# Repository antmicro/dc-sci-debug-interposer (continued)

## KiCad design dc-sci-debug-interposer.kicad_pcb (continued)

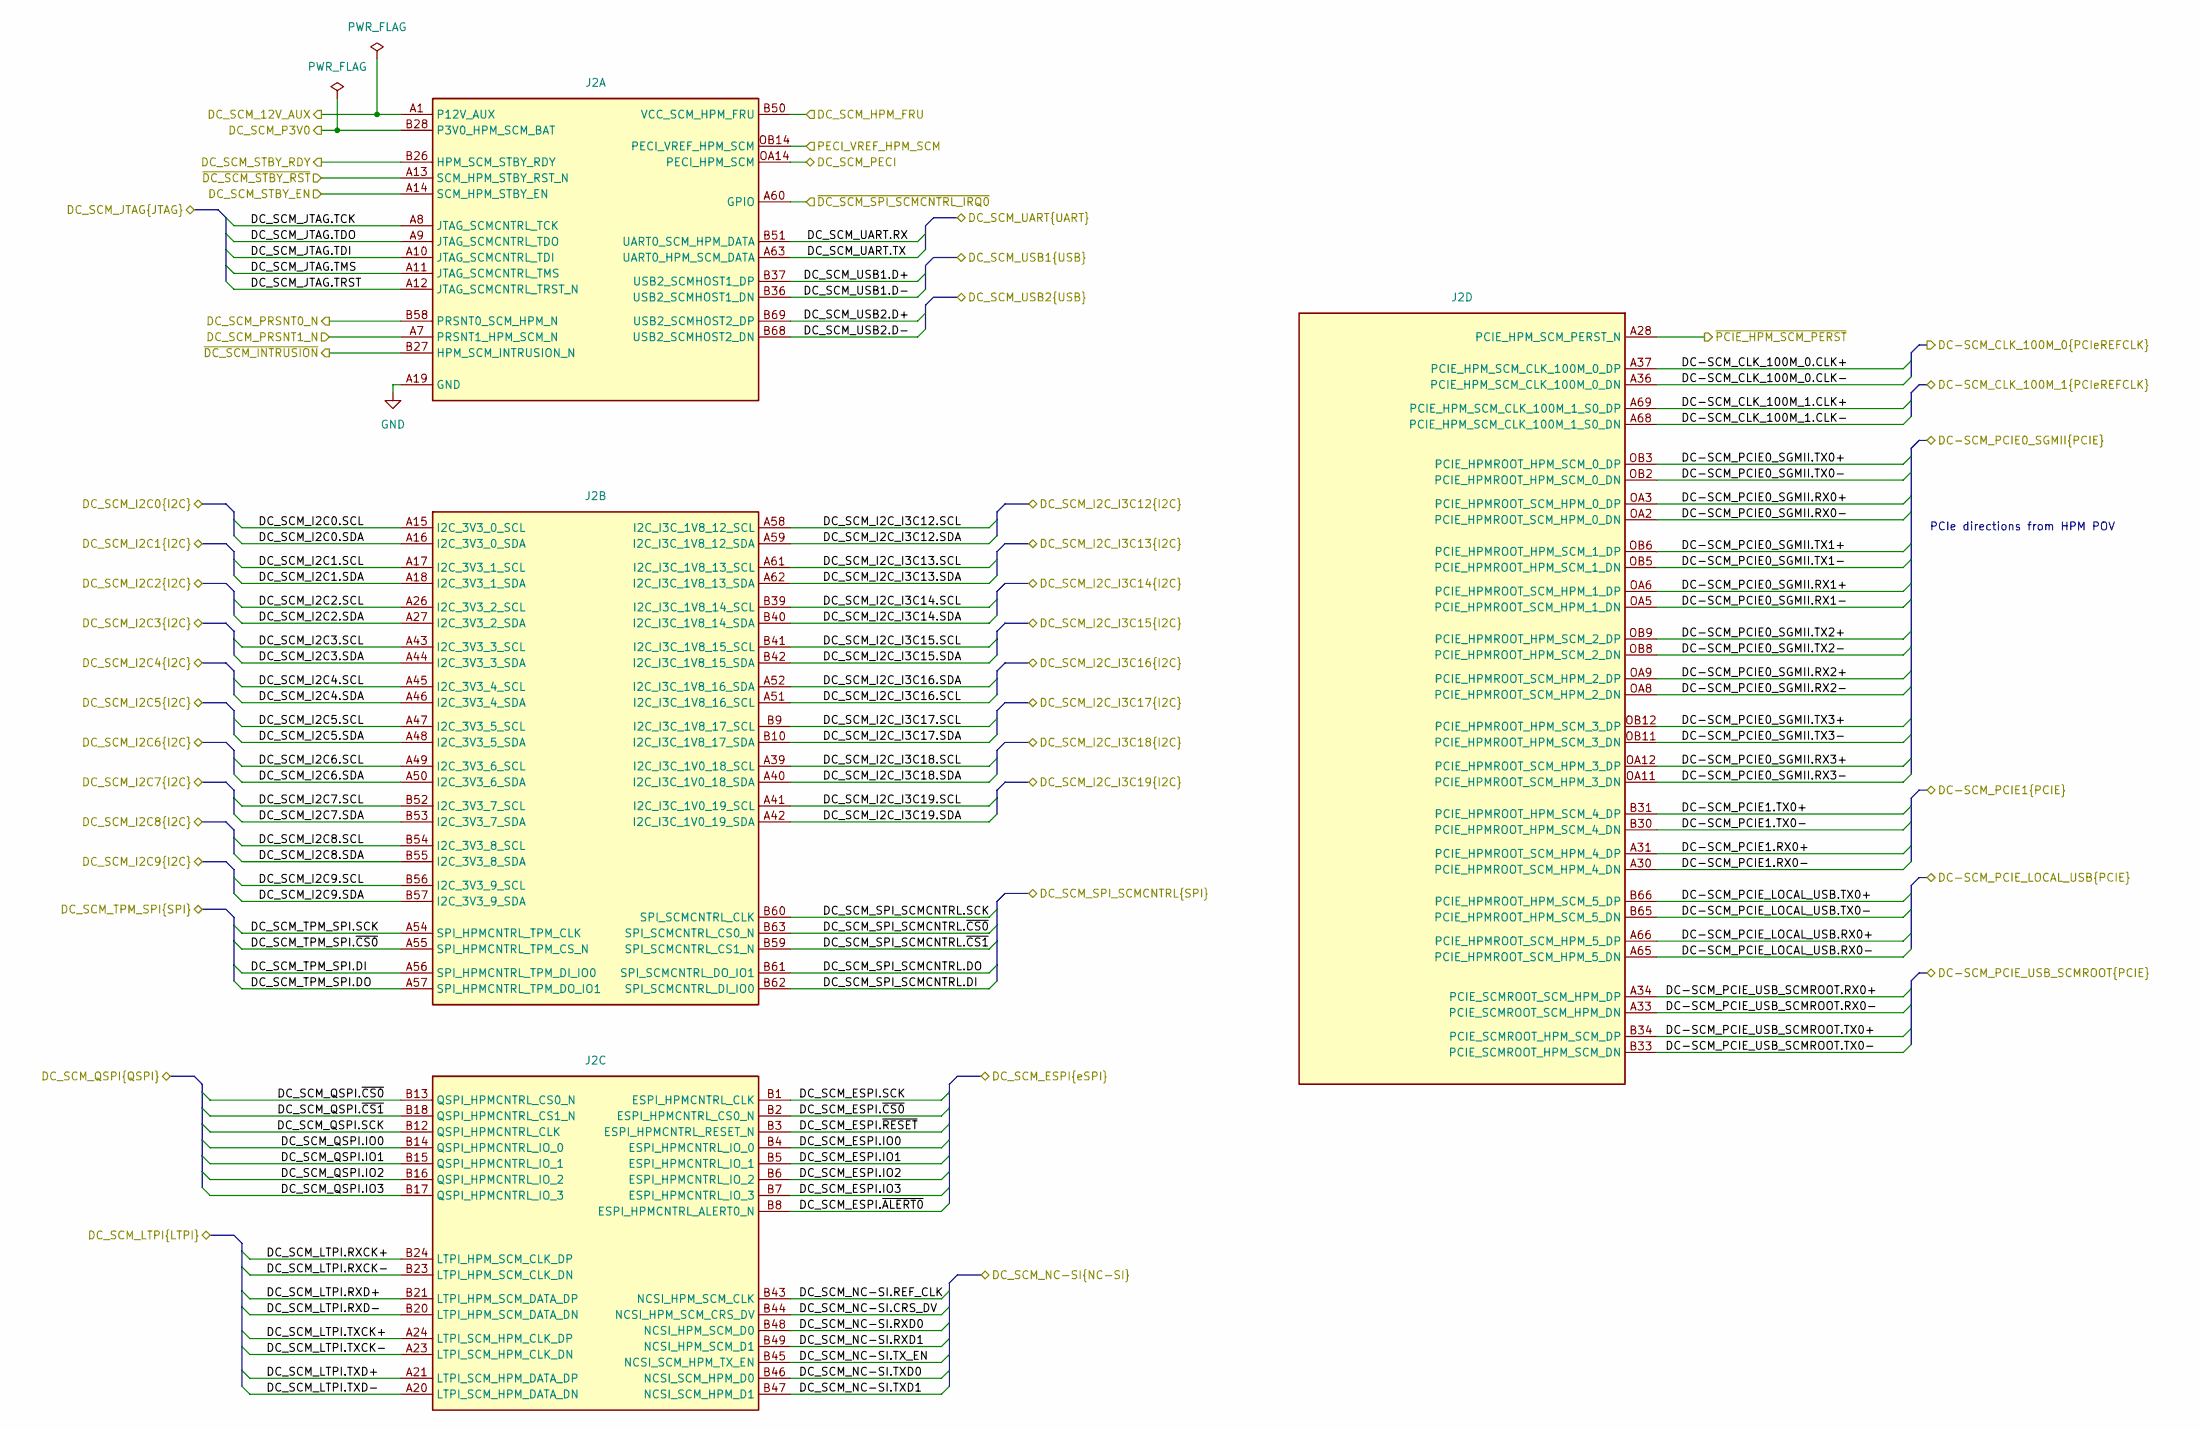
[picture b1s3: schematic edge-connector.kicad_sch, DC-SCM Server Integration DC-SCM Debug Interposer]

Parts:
J2: PCB-Edge_DC-SCM-2.1_2x84_Rev-1-1

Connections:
/DC-SCI edge connector/DC-SCM_CLK_100M_0.CLK+: J2.A37 (PCIE_HPM_SCM_CLK_100M_0_DP); also elsewhere on the board
/DC-SCI edge connector/DC-SCM_CLK_100M_0.CLK-: J2.A36 (PCIE_HPM_SCM_CLK_100M_0_DN); also elsewhere on the board
/DC-SCI edge connector/DC-SCM_CLK_100M_1.CLK+: J2.A69 (PCIE_HPM_SCM_CLK_100M_1_S0_DP); also elsewhere on the board
/DC-SCI edge connector/DC-SCM_CLK_100M_1.CLK-: J2.A68 (PCIE_HPM_SCM_CLK_100M_1_S0_DN); also elsewhere on the board
/DC-SCI edge connector/DC-SCM_PCIE0_SGMII.RX0+: J2.OA3 (PCIE_HPMROOT_SCM_HPM_0_DP); also elsewhere on the board
/DC-SCI edge connector/DC-SCM_PCIE0_SGMII.RX0-: J2.OA2 (PCIE_HPMROOT_SCM_HPM_0_DN); also elsewhere on the board
/DC-SCI edge connector/DC-SCM_PCIE0_SGMII.RX1+: J2.OA6 (PCIE_HPMROOT_SCM_HPM_1_DP); also elsewhere on the board
/DC-SCI edge connector/DC-SCM_PCIE0_SGMII.RX1-: J2.OA5 (PCIE_HPMROOT_SCM_HPM_1_DN); also elsewhere on the board
/DC-SCI edge connector/DC-SCM_PCIE0_SGMII.RX2+: J2.OA9 (PCIE_HPMROOT_SCM_HPM_2_DP); also elsewhere on the board
/DC-SCI edge connector/DC-SCM_PCIE0_SGMII.RX2-: J2.OA8 (PCIE_HPMROOT_SCM_HPM_2_DN); also elsewhere on the board
/DC-SCI edge connector/DC-SCM_PCIE0_SGMII.RX3+: J2.OA12 (PCIE_HPMROOT_SCM_HPM_3_DP); also elsewhere on the board
/DC-SCI edge connector/DC-SCM_PCIE0_SGMII.RX3-: J2.OA11 (PCIE_HPMROOT_SCM_HPM_3_DN); also elsewhere on the board
/DC-SCI edge connector/DC-SCM_PCIE0_SGMII.TX0+: J2.OB3 (PCIE_HPMROOT_HPM_SCM_0_DP); also elsewhere on the board
/DC-SCI edge connector/DC-SCM_PCIE0_SGMII.TX0-: J2.OB2 (PCIE_HPMROOT_HPM_SCM_0_DN); also elsewhere on the board
/DC-SCI edge connector/DC-SCM_PCIE0_SGMII.TX1+: J2.OB6 (PCIE_HPMROOT_HPM_SCM_1_DP); also elsewhere on the board
/DC-SCI edge connector/DC-SCM_PCIE0_SGMII.TX1-: J2.OB5 (PCIE_HPMROOT_HPM_SCM_1_DN); also elsewhere on the board
/DC-SCI edge connector/DC-SCM_PCIE0_SGMII.TX2+: J2.OB9 (PCIE_HPMROOT_HPM_SCM_2_DP); also elsewhere on the board
/DC-SCI edge connector/DC-SCM_PCIE0_SGMII.TX2-: J2.OB8 (PCIE_HPMROOT_HPM_SCM_2_DN); also elsewhere on the board
/DC-SCI edge connector/DC-SCM_PCIE0_SGMII.TX3+: J2.OB12 (PCIE_HPMROOT_HPM_SCM_3_DP); also elsewhere on the board
/DC-SCI edge connector/DC-SCM_PCIE0_SGMII.TX3-: J2.OB11 (PCIE_HPMROOT_HPM_SCM_3_DN); also elsewhere on the board
/DC-SCI edge connector/DC-SCM_PCIE1.RX0+: J2.A31 (PCIE_HPMROOT_SCM_HPM_4_DP); also elsewhere on the board
/DC-SCI edge connector/DC-SCM_PCIE1.RX0-: J2.A30 (PCIE_HPMROOT_SCM_HPM_4_DN); also elsewhere on the board
/DC-SCI edge connector/DC-SCM_PCIE1.TX0+: J2.B31 (PCIE_HPMROOT_HPM_SCM_4_DP); also elsewhere on the board
/DC-SCI edge connector/DC-SCM_PCIE1.TX0-: J2.B30 (PCIE_HPMROOT_HPM_SCM_4_DN); also elsewhere on the board
/DC-SCI edge connector/DC-SCM_PCIE_LOCAL_USB.RX0+: J2.A66 (PCIE_HPMROOT_SCM_HPM_5_DP); also elsewhere on the board
/DC-SCI edge connector/DC-SCM_PCIE_LOCAL_USB.RX0-: J2.A65 (PCIE_HPMROOT_SCM_HPM_5_DN); also elsewhere on the board
/DC-SCI edge connector/DC-SCM_PCIE_LOCAL_USB.TX0+: J2.B66 (PCIE_HPMROOT_HPM_SCM_5_DP); also elsewhere on the board
/DC-SCI edge connector/DC-SCM_PCIE_LOCAL_USB.TX0-: J2.B65 (PCIE_HPMROOT_HPM_SCM_5_DN); also elsewhere on the board
/DC-SCI edge connector/DC-SCM_PCIE_USB_SCMROOT.RX0+: J2.A34 (PCIE_SCMROOT_SCM_HPM_DP); also elsewhere on the board
/DC-SCI edge connector/DC-SCM_PCIE_USB_SCMROOT.RX0-: J2.A33 (PCIE_SCMROOT_SCM_HPM_DN); also elsewhere on the board
/DC-SCI edge connector/DC-SCM_PCIE_USB_SCMROOT.TX0+: J2.B34 (PCIE_SCMROOT_HPM_SCM_DP); also elsewhere on the board
/DC-SCI edge connector/DC-SCM_PCIE_USB_SCMROOT.TX0-: J2.B33 (PCIE_SCMROOT_HPM_SCM_DN); also elsewhere on the board
/DC-SCI edge connector/DC_SCM_12V_AUX: J2.A1 (P12V_AUX), J2.A2 (P12V_AUX), J2.A3 (P12V_AUX), J2.A4 (P12V_AUX); also elsewhere on the board
/DC-SCI edge connector/DC_SCM_ESPI.IO0: J2.B4 (ESPI_HPMCNTRL_IO_0); also elsewhere on the board
/DC-SCI edge connector/DC_SCM_ESPI.IO1: J2.B5 (ESPI_HPMCNTRL_IO_1); also elsewhere on the board
/DC-SCI edge connector/DC_SCM_ESPI.IO2: J2.B6 (ESPI_HPMCNTRL_IO_2); also elsewhere on the board
/DC-SCI edge connector/DC_SCM_ESPI.IO3: J2.B7 (ESPI_HPMCNTRL_IO_3); also elsewhere on the board
/DC-SCI edge connector/DC_SCM_ESPI.SCK: J2.B1 (ESPI_HPMCNTRL_CLK); also elsewhere on the board
/DC-SCI edge connector/DC_SCM_ESPI.~ALERT0: J2.B8 (ESPI_HPMCNTRL_ALERT0_N); also elsewhere on the board
/DC-SCI edge connector/DC_SCM_ESPI.~CS0: J2.B2 (ESPI_HPMCNTRL_CS0_N); also elsewhere on the board
/DC-SCI edge connector/DC_SCM_ESPI.~RESET: J2.B3 (ESPI_HPMCNTRL_RESET_N); also elsewhere on the board
/DC-SCI edge connector/DC_SCM_HPM_FRU: J2.B50 (VCC_SCM_HPM_FRU); also elsewhere on the board
/DC-SCI edge connector/DC_SCM_I2C0.SCL: J2.A15 (I2C_3V3_0_SCL); also elsewhere on the board
/DC-SCI edge connector/DC_SCM_I2C0.SDA: J2.A16 (I2C_3V3_0_SDA); also elsewhere on the board
/DC-SCI edge connector/DC_SCM_I2C1.SCL: J2.A17 (I2C_3V3_1_SCL); also elsewhere on the board
/DC-SCI edge connector/DC_SCM_I2C1.SDA: J2.A18 (I2C_3V3_1_SDA); also elsewhere on the board
/DC-SCI edge connector/DC_SCM_I2C2.SCL: J2.A26 (I2C_3V3_2_SCL); also elsewhere on the board
/DC-SCI edge connector/DC_SCM_I2C2.SDA: J2.A27 (I2C_3V3_2_SDA); also elsewhere on the board
/DC-SCI edge connector/DC_SCM_I2C3.SCL: J2.A43 (I2C_3V3_3_SCL); also elsewhere on the board
/DC-SCI edge connector/DC_SCM_I2C3.SDA: J2.A44 (I2C_3V3_3_SDA); also elsewhere on the board
/DC-SCI edge connector/DC_SCM_I2C4.SCL: J2.A45 (I2C_3V3_4_SCL); also elsewhere on the board
/DC-SCI edge connector/DC_SCM_I2C4.SDA: J2.A46 (I2C_3V3_4_SDA); also elsewhere on the board
/DC-SCI edge connector/DC_SCM_I2C5.SCL: J2.A47 (I2C_3V3_5_SCL); also elsewhere on the board
/DC-SCI edge connector/DC_SCM_I2C5.SDA: J2.A48 (I2C_3V3_5_SDA); also elsewhere on the board
/DC-SCI edge connector/DC_SCM_I2C6.SCL: J2.A49 (I2C_3V3_6_SCL); also elsewhere on the board
/DC-SCI edge connector/DC_SCM_I2C6.SDA: J2.A50 (I2C_3V3_6_SDA); also elsewhere on the board
/DC-SCI edge connector/DC_SCM_I2C7.SCL: J2.B52 (I2C_3V3_7_SCL); also elsewhere on the board
/DC-SCI edge connector/DC_SCM_I2C7.SDA: J2.B53 (I2C_3V3_7_SDA); also elsewhere on the board
/DC-SCI edge connector/DC_SCM_I2C8.SCL: J2.B54 (I2C_3V3_8_SCL); also elsewhere on the board
/DC-SCI edge connector/DC_SCM_I2C8.SDA: J2.B55 (I2C_3V3_8_SDA); also elsewhere on the board
/DC-SCI edge connector/DC_SCM_I2C9.SCL: J2.B56 (I2C_3V3_9_SCL); also elsewhere on the board
/DC-SCI edge connector/DC_SCM_I2C9.SDA: J2.B57 (I2C_3V3_9_SDA); also elsewhere on the board
/DC-SCI edge connector/DC_SCM_I2C_I3C12.SCL: J2.A58 (I2C_I3C_1V8_12_SCL); also elsewhere on the board
/DC-SCI edge connector/DC_SCM_I2C_I3C12.SDA: J2.A59 (I2C_I3C_1V8_12_SDA); also elsewhere on the board
/DC-SCI edge connector/DC_SCM_I2C_I3C13.SCL: J2.A61 (I2C_I3C_1V8_13_SCL); also elsewhere on the board
/DC-SCI edge connector/DC_SCM_I2C_I3C13.SDA: J2.A62 (I2C_I3C_1V8_13_SDA); also elsewhere on the board
/DC-SCI edge connector/DC_SCM_I2C_I3C14.SCL: J2.B39 (I2C_I3C_1V8_14_SCL); also elsewhere on the board
/DC-SCI edge connector/DC_SCM_I2C_I3C14.SDA: J2.B40 (I2C_I3C_1V8_14_SDA); also elsewhere on the board
/DC-SCI edge connector/DC_SCM_I2C_I3C15.SCL: J2.B41 (I2C_I3C_1V8_15_SCL); also elsewhere on the board
/DC-SCI edge connector/DC_SCM_I2C_I3C15.SDA: J2.B42 (I2C_I3C_1V8_15_SDA); also elsewhere on the board
/DC-SCI edge connector/DC_SCM_I2C_I3C16.SCL: J2.A51 (I2C_I3C_1V8_16_SCL); also elsewhere on the board
/DC-SCI edge connector/DC_SCM_I2C_I3C16.SDA: J2.A52 (I2C_I3C_1V8_16_SDA); also elsewhere on the board
/DC-SCI edge connector/DC_SCM_I2C_I3C17.SCL: J2.B9 (I2C_I3C_1V8_17_SCL); also elsewhere on the board
/DC-SCI edge connector/DC_SCM_I2C_I3C17.SDA: J2.B10 (I2C_I3C_1V8_17_SDA); also elsewhere on the board
/DC-SCI edge connector/DC_SCM_I2C_I3C18.SCL: J2.A39 (I2C_I3C_1V0_18_SCL); also elsewhere on the board
/DC-SCI edge connector/DC_SCM_I2C_I3C18.SDA: J2.A40 (I2C_I3C_1V0_18_SDA); also elsewhere on the board
/DC-SCI edge connector/DC_SCM_I2C_I3C19.SCL: J2.A41 (I2C_I3C_1V0_19_SCL); also elsewhere on the board
/DC-SCI edge connector/DC_SCM_I2C_I3C19.SDA: J2.A42 (I2C_I3C_1V0_19_SDA); also elsewhere on the board
/DC-SCI edge connector/DC_SCM_JTAG.TCK: J2.A8 (JTAG_SCMCNTRL_TCK); also elsewhere on the board
/DC-SCI edge connector/DC_SCM_JTAG.TDI: J2.A10 (JTAG_SCMCNTRL_TDI); also elsewhere on the board
/DC-SCI edge connector/DC_SCM_JTAG.TDO: J2.A9 (JTAG_SCMCNTRL_TDO); also elsewhere on the board
/DC-SCI edge connector/DC_SCM_JTAG.TMS: J2.A11 (JTAG_SCMCNTRL_TMS); also elsewhere on the board
/DC-SCI edge connector/DC_SCM_JTAG.TRST: J2.A12 (JTAG_SCMCNTRL_TRST_N); also elsewhere on the board
/DC-SCI edge connector/DC_SCM_LTPI.RXCK+: J2.B24 (LTPI_HPM_SCM_CLK_DP); also elsewhere on the board
/DC-SCI edge connector/DC_SCM_LTPI.RXCK-: J2.B23 (LTPI_HPM_SCM_CLK_DN); also elsewhere on the board
/DC-SCI edge connector/DC_SCM_LTPI.RXD+: J2.B21 (LTPI_HPM_SCM_DATA_DP); also elsewhere on the board
/DC-SCI edge connector/DC_SCM_LTPI.RXD-: J2.B20 (LTPI_HPM_SCM_DATA_DN); also elsewhere on the board
/DC-SCI edge connector/DC_SCM_LTPI.TXCK+: J2.A24 (LTPI_SCM_HPM_CLK_DP); also elsewhere on the board
/DC-SCI edge connector/DC_SCM_LTPI.TXCK-: J2.A23 (LTPI_SCM_HPM_CLK_DN); also elsewhere on the board
/DC-SCI edge connector/DC_SCM_LTPI.TXD+: J2.A21 (LTPI_SCM_HPM_DATA_DP); also elsewhere on the board
/DC-SCI edge connector/DC_SCM_LTPI.TXD-: J2.A20 (LTPI_SCM_HPM_DATA_DN); also elsewhere on the board
/DC-SCI edge connector/DC_SCM_NC-SI.CRS_DV: J2.B44 (NCSI_HPM_SCM_CRS_DV); also elsewhere on the board
/DC-SCI edge connector/DC_SCM_NC-SI.REF_CLK: J2.B43 (NCSI_HPM_SCM_CLK); also elsewhere on the board
/DC-SCI edge connector/DC_SCM_NC-SI.RXD0: J2.B48 (NCSI_HPM_SCM_D0); also elsewhere on the board
/DC-SCI edge connector/DC_SCM_NC-SI.RXD1: J2.B49 (NCSI_HPM_SCM_D1); also elsewhere on the board
/DC-SCI edge connector/DC_SCM_NC-SI.TXD0: J2.B46 (NCSI_SCM_HPM_D0); also elsewhere on the board
/DC-SCI edge connector/DC_SCM_NC-SI.TXD1: J2.B47 (NCSI_SCM_HPM_D1); also elsewhere on the board
/DC-SCI edge connector/DC_SCM_NC-SI.TX_EN: J2.B45 (NCSI_SCM_HPM_TX_EN); also elsewhere on the board
/DC-SCI edge connector/DC_SCM_P3V0: J2.B28 (P3V0_HPM_SCM_BAT); also elsewhere on the board
/DC-SCI edge connector/DC_SCM_PECI: J2.OA14 (PECI_HPM_SCM); also elsewhere on the board
/DC-SCI edge connector/DC_SCM_PRSNT0_N: J2.B58 (PRSNT0_SCM_HPM_N); also elsewhere on the board
/DC-SCI edge connector/DC_SCM_PRSNT1_N: J2.A7 (PRSNT1_HPM_SCM_N); also elsewhere on the board
/DC-SCI edge connector/DC_SCM_QSPI.IO0: J2.B14 (QSPI_HPMCNTRL_IO_0); also elsewhere on the board
/DC-SCI edge connector/DC_SCM_QSPI.IO1: J2.B15 (QSPI_HPMCNTRL_IO_1); also elsewhere on the board
/DC-SCI edge connector/DC_SCM_QSPI.IO2: J2.B16 (QSPI_HPMCNTRL_IO_2); also elsewhere on the board
/DC-SCI edge connector/DC_SCM_QSPI.IO3: J2.B17 (QSPI_HPMCNTRL_IO_3); also elsewhere on the board
/DC-SCI edge connector/DC_SCM_QSPI.SCK: J2.B12 (QSPI_HPMCNTRL_CLK); also elsewhere on the board
/DC-SCI edge connector/DC_SCM_QSPI.~CS0: J2.B13 (QSPI_HPMCNTRL_CS0_N); also elsewhere on the board
/DC-SCI edge connector/DC_SCM_QSPI.~CS1: J2.B18 (QSPI_HPMCNTRL_CS1_N); also elsewhere on the board
/DC-SCI edge connector/DC_SCM_SPI_SCMCNTRL.DI: J2.B62 (SPI_SCMCNTRL_DI_IO0); also elsewhere on the board
/DC-SCI edge connector/DC_SCM_SPI_SCMCNTRL.DO: J2.B61 (SPI_SCMCNTRL_DO_IO1); also elsewhere on the board
/DC-SCI edge connector/DC_SCM_SPI_SCMCNTRL.SCK: J2.B60 (SPI_SCMCNTRL_CLK); also elsewhere on the board
/DC-SCI edge connector/DC_SCM_SPI_SCMCNTRL.~CS0: J2.B63 (SPI_SCMCNTRL_CS0_N); also elsewhere on the board
/DC-SCI edge connector/DC_SCM_SPI_SCMCNTRL.~CS1: J2.B59 (SPI_SCMCNTRL_CS1_N); also elsewhere on the board
/DC-SCI edge connector/DC_SCM_STBY_EN: J2.A14 (SCM_HPM_STBY_EN); also elsewhere on the board
/DC-SCI edge connector/DC_SCM_STBY_RDY: J2.B26 (HPM_SCM_STBY_RDY); also elsewhere on the board
/DC-SCI edge connector/DC_SCM_TPM_SPI.DI: J2.A56 (SPI_HPMCNTRL_TPM_DI_IO0); also elsewhere on the board
/DC-SCI edge connector/DC_SCM_TPM_SPI.DO: J2.A57 (SPI_HPMCNTRL_TPM_DO_IO1); also elsewhere on the board
/DC-SCI edge connector/DC_SCM_TPM_SPI.SCK: J2.A54 (SPI_HPMCNTRL_TPM_CLK); also elsewhere on the board
/DC-SCI edge connector/DC_SCM_TPM_SPI.~CS0: J2.A55 (SPI_HPMCNTRL_TPM_CS_N); also elsewhere on the board
/DC-SCI edge connector/DC_SCM_UART.RX: J2.B51 (UART0_SCM_HPM_DATA); also elsewhere on the board
/DC-SCI edge connector/DC_SCM_UART.TX: J2.A63 (UART0_HPM_SCM_DATA); also elsewhere on the board
/DC-SCI edge connector/DC_SCM_USB1.D+: J2.B37 (USB2_SCMHOST1_DP); also elsewhere on the board
/DC-SCI edge connector/DC_SCM_USB1.D-: J2.B36 (USB2_SCMHOST1_DN); also elsewhere on the board
/DC-SCI edge connector/DC_SCM_USB2.D+: J2.B69 (USB2_SCMHOST2_DP); also elsewhere on the board
/DC-SCI edge connector/DC_SCM_USB2.D-: J2.B68 (USB2_SCMHOST2_DN); also elsewhere on the board
/DC-SCI edge connector/PECI_VREF_HPM_SCM: J2.OB14 (PECI_VREF_HPM_SCM); also elsewhere on the board
/DC-SCI edge connector/~DC_SCM_INTRUSION: J2.B27 (HPM_SCM_INTRUSION_N); also elsewhere on the board
/DC-SCI edge connector/~DC_SCM_SPI_SCMCNTRL_IRQ0: J2.A60 (GPIO); also elsewhere on the board
/DC-SCI edge connector/~DC_SCM_STBY_RST: J2.A13 (SCM_HPM_STBY_RST_N); also elsewhere on the board
/DC-SCI edge connector/~PCIE_HPM_SCM_PERST: J2.A28 (PCIE_HPM_SCM_PERST_N); also elsewhere on the board
GND: J2.A5 (GND), J2.A6 (GND), J2.A19 (GND), J2.A22 (GND), J2.A25 (GND), J2.A29 (GND), J2.A32 (GND), J2.A35 (GND), J2.A38 (GND), J2.A53 (GND), J2.A64 (GND), J2.A67 (GND), J2.A70 (GND), J2.B11 (GND), J2.B19 (GND), J2.B22 (GND), J2.B25 (GND), J2.B29 (GND), J2.B32 (GND), J2.B35 (GND), J2.B38 (GND), J2.B64 (GND), J2.B67 (GND), J2.B70 (GND), J2.OA1 (GND), J2.OA4 (GND), J2.OA7 (GND), J2.OA10 (GND), J2.OA13 (GND), J2.OB1 (GND), J2.OB4 (GND), J2.OB7 (GND), J2.OB10 (GND), J2.OB13 (GND); also elsewhere on the board

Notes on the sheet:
PCIe directions from HPM POV

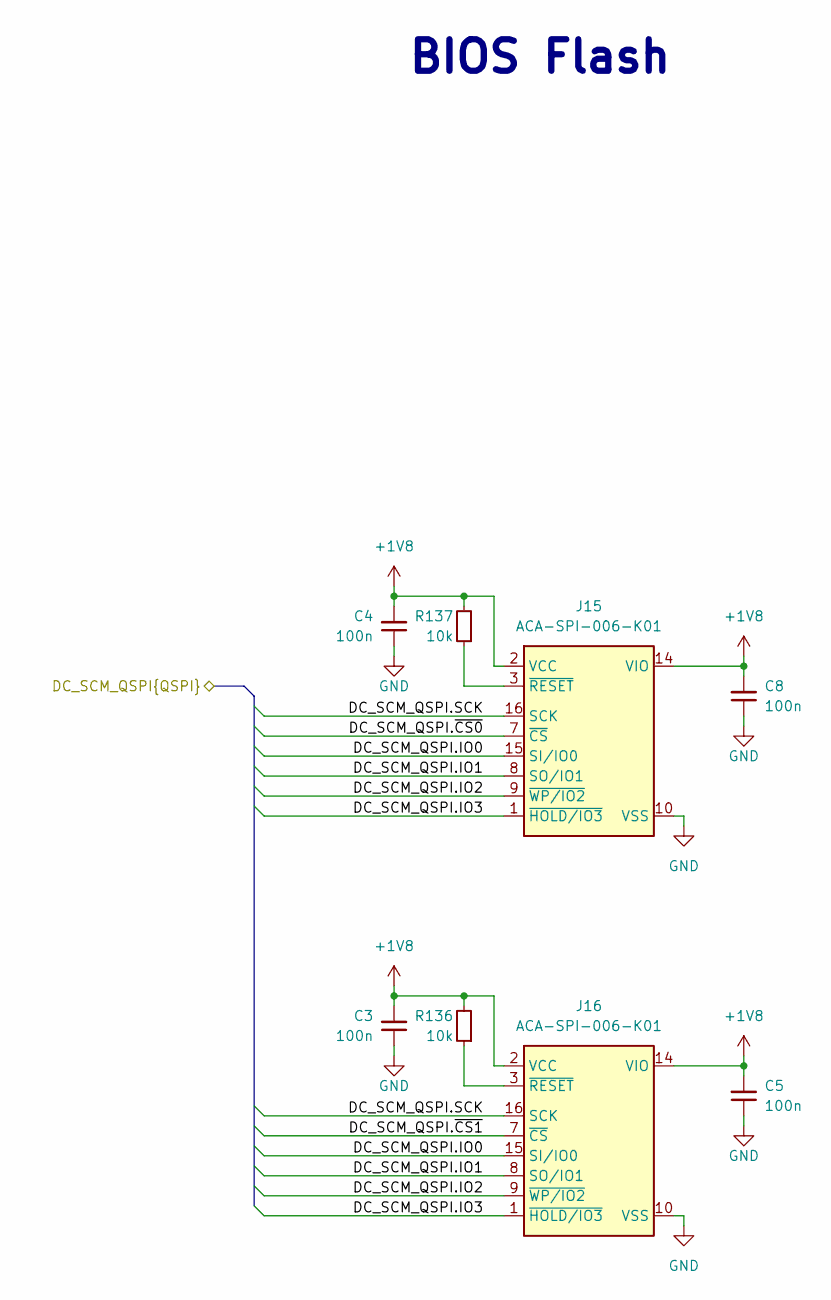
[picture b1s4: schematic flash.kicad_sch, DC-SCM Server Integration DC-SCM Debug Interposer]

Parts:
C3, C4, C5, C8: C_100n_0402; C_0402_1005Metric; Voltage 50V; MPN GRM155R61H104KE14D
J15, J16: Socket_SOP2-16_ACA-SPI-006-K01_Flash_CUSTOM; Socket_SOP2-16_ACA-SPI-006-K01; MPN ACA-SPI-006-K01
R136, R137: R_10k_0402; R_0402_1005Metric; Tolerance 1%; MPN CR0402-FX-1002GLF

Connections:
+1V8: C3.2, C4.2, C5.2, C8.2, J15.2 (VCC), J15.14 (VIO), J16.2 (VCC), J16.14 (VIO), R136.2, R137.2; also elsewhere on the board
/DC-SCI edge connector/DC_SCM_QSPI.IO0: J15.15 (SI/IO0), J16.15 (SI/IO0); also elsewhere on the board
/DC-SCI edge connector/DC_SCM_QSPI.IO1: J15.8 (SO/IO1), J16.8 (SO/IO1); also elsewhere on the board
/DC-SCI edge connector/DC_SCM_QSPI.IO2: J15.9 (~WP/IO2), J16.9 (~WP/IO2); also elsewhere on the board
/DC-SCI edge connector/DC_SCM_QSPI.IO3: J15.1 (~HOLD/IO3), J16.1 (~HOLD/IO3); also elsewhere on the board
/DC-SCI edge connector/DC_SCM_QSPI.SCK: J15.16 (SCK), J16.16 (SCK); also elsewhere on the board
/DC-SCI edge connector/DC_SCM_QSPI.~CS0: J15.7 (~CS); also elsewhere on the board
/DC-SCI edge connector/DC_SCM_QSPI.~CS1: J16.7 (~CS); also elsewhere on the board
GND: C3.1, C4.1, C5.1, C8.1, J15.10 (VSS), J16.10 (VSS); also elsewhere on the board
unnamed: J15.3 (~RESET), R137.1
unnamed: J16.3 (~RESET), R136.1

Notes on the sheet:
BIOS Flash

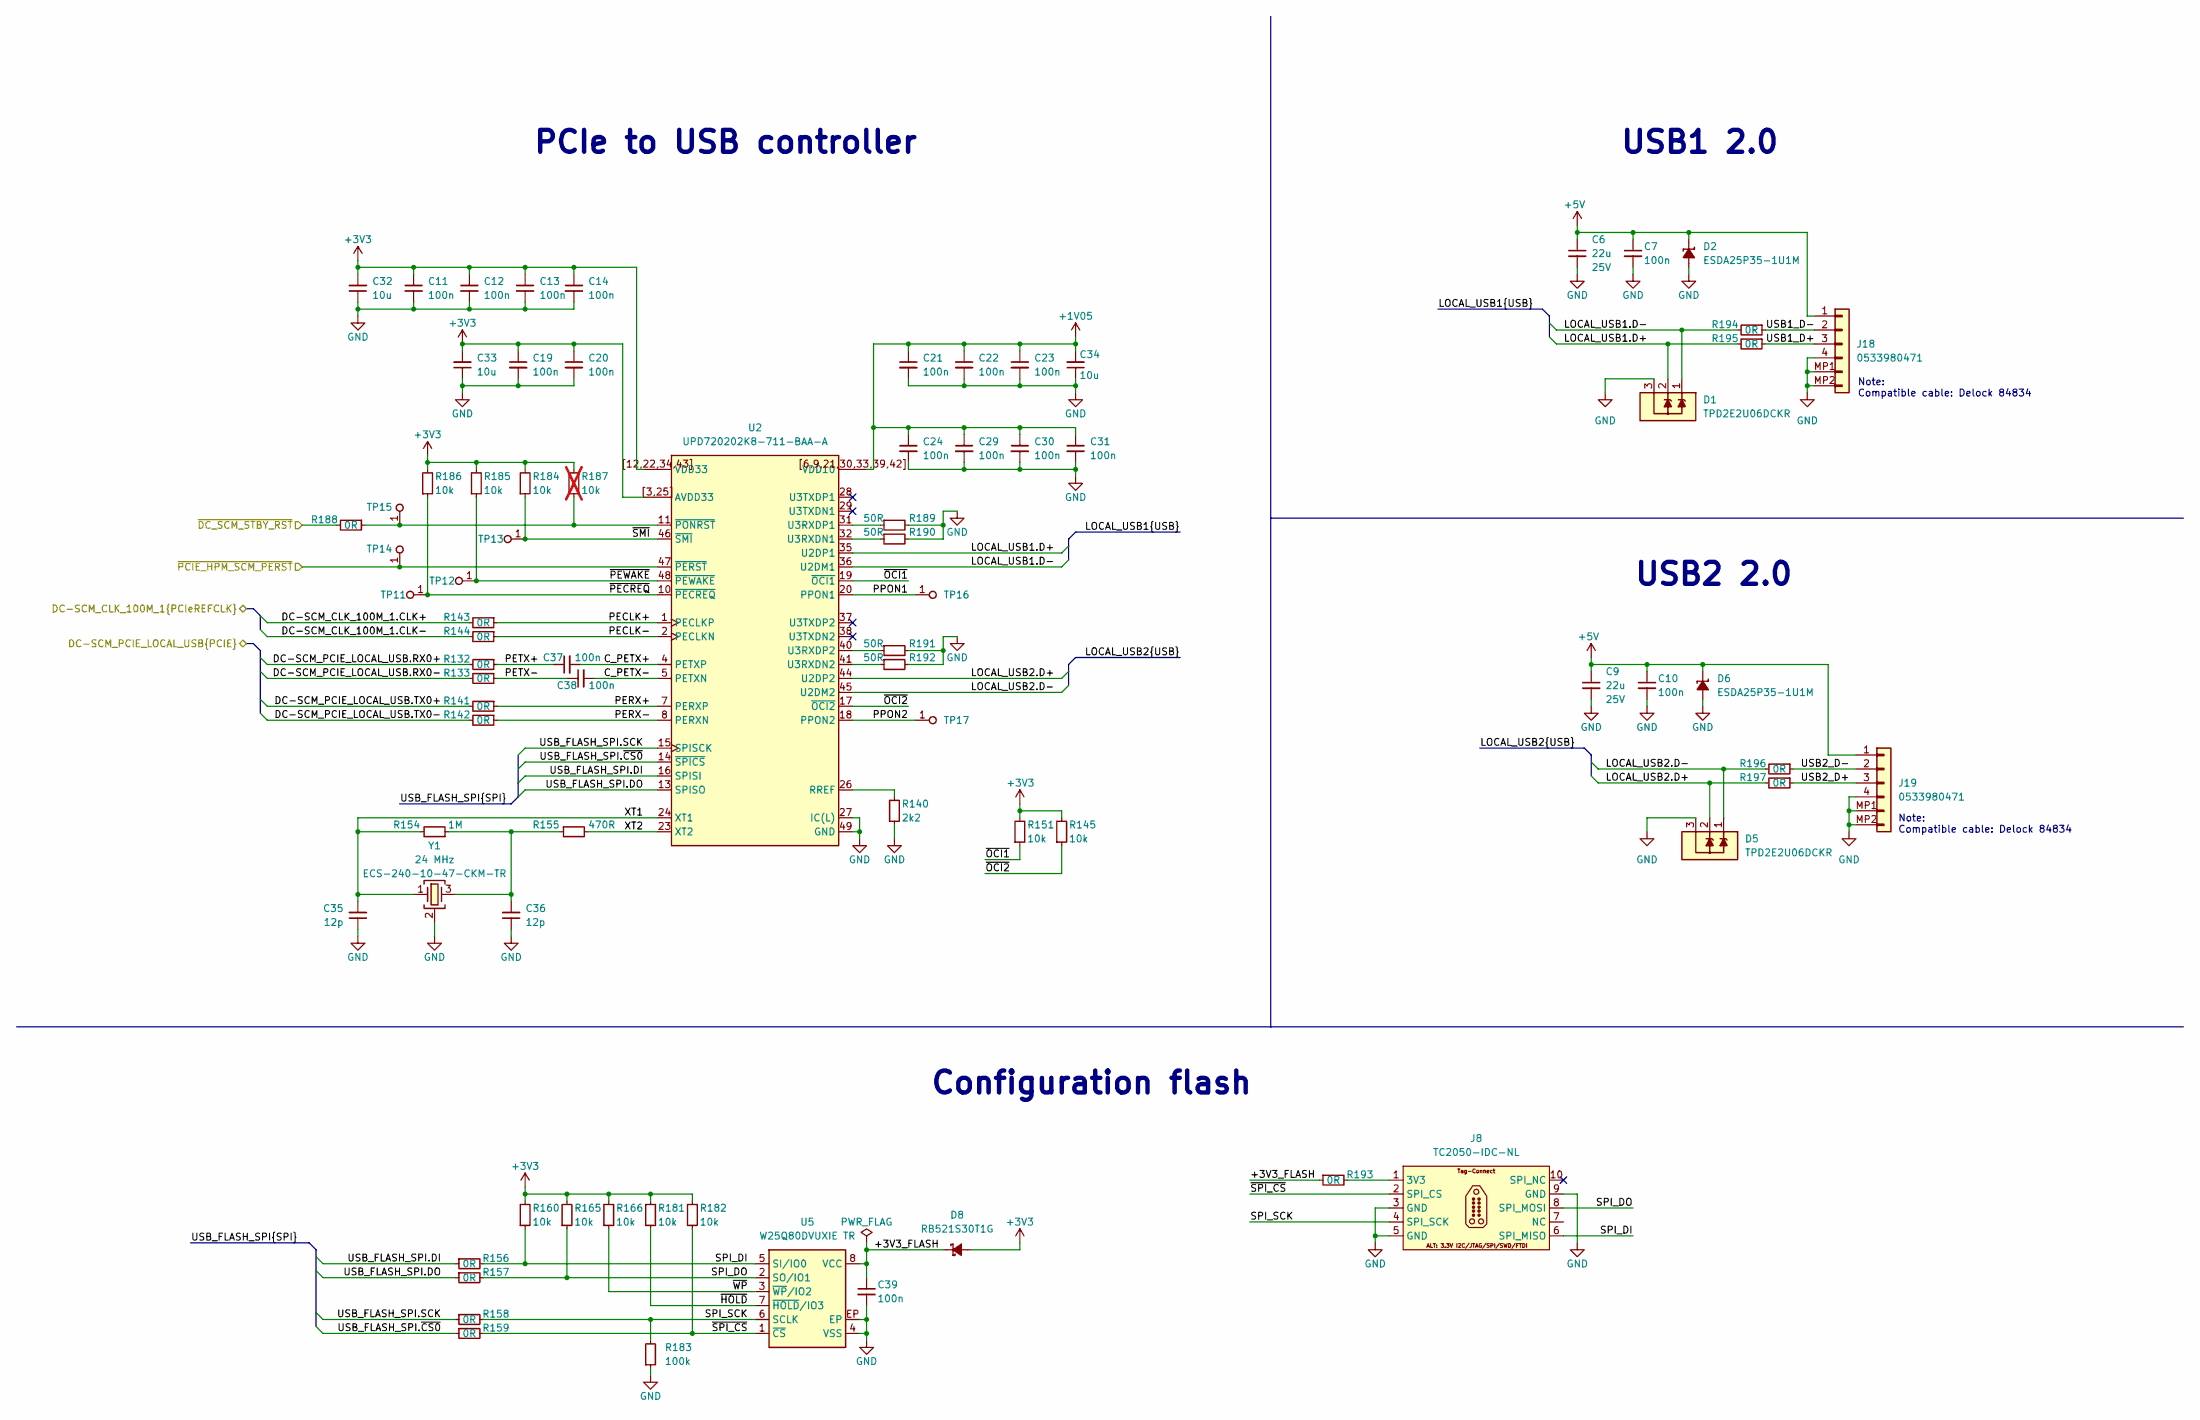
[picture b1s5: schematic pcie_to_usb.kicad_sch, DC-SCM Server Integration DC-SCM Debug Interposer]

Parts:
C6, C9: C_22u_25V_0805; C_0805_2012Metric; Voltage 25V; MPN CL21A226MAYNNNE
C7, C10, C11, C12, C13, C14, C19, C20, C21, C22, C23, C24, C29, C30, C31, C37, C38, C39: C_100n_0402; C_0402_1005Metric; Voltage 50V; MPN GRM155R61H104KE14D
C32, C33, C34: C_10u_10V_0402; C_0402_1005Metric; Voltage 10V; MPN GRM155R61A106ME11D
C35, C36: C_12p_0402; C_0402_1005Metric; MPN CGA2B2C0G1H120J050BA
D1, D5: TPD2E2U06_SC70; SC70-3; MPN TPD2E2U06DCKR
D2, D6: ESDA25P35-1U1M; QFN-2L_1.6x1x0.55mm; MPN ESDA25P35-1U1M
D8: RB521S30T1G; SOD-523; MPN RB521S30T1G
J8: Tag-Connect_TC2050-IDC-NL_2x5_P1.27mm; MPN TC2050-IDC-NL
J18, J19: Molex_PicoBlade_1x4_0533980471; Conn_Molex_PicoBlade_1x4_0533980471; MPN 0533980471
R132, R133, R141, R142, R143, R144, R156, R157, R158, R159, R188, R193, R194, R195, R196, R197: R_0R_0402; R_0402_1005Metric; MPN ERJ2GE0R00X
R140: R_2k2_0402; R_0402_1005Metric; Tolerance 1%; MPN CR0402-FX-2201GLF
R145, R151, R160, R165, R166, R181, R182, R184, R185, R186: R_10k_0402; R_0402_1005Metric; Tolerance 1%; MPN CR0402-FX-1002GLF
R154: R_1M_0402; R_0402_1005Metric; Tolerance 1%; MPN CR0402-FX-1004GLF
R155: R_470R_0402; R_0402_1005Metric; Tolerance 1%; MPN CR0402-FX-4700GLF
R183: R_100k_0402; R_0402_1005Metric; Tolerance 1%; MPN CR0402-FX-1003GLF
R187: R_10k_0402; R_0402_1005Metric; Tolerance 1%; MPN CR0402-FX-1002GLF; not fitted
R189, R190, R191, R192: R_50R_0402; R_0402_1005Metric; Tolerance 1%; MPN CR0402-FX-50R0GLF
TP11, TP12, TP13, TP14, TP15, TP16, TP17: TP_0.75mm_SMD; TP_SMD_0.75mm
U2: UPD720202K8-711-BAA-A; QFN-48-1EP_7x7mm; MPN UPD720202K8-711-BAA-A
U5: W25Q80DV_USON; USON-8_2x3mm_P0.5mm; MPN W25Q80DVUXIE TR
Y1: Resonator_24MHz_ECX-1247; Resonator_SMD_ECS_ECX-1247_1.6x1.2x0.3mm; MPN ECS-240-10-47-CKM-TR

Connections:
+1V05: C21.1, C22.1, C23.1, C24.1, C29.1, C30.1, C31.1, C34.2, U2.6 (VDD10), U2.9 (VDD10), U2.21 (VDD10), U2.30 (VDD10), U2.33 (VDD10), U2.39 (VDD10), U2.42 (VDD10), U2.[6,9,21,30,33,39,42] (VDD10); also elsewhere on the board
+3V3: C11.1, C12.1, C13.1, C14.1, C19.1, C20.1, C32.2, C33.2, D8.2 (A), R145.2, R151.2, R160.2, R165.2, R166.2, R181.2, R182.2, R184.2, R185.2, R186.2, R187.2, U2.3 (AVDD33), U2.12 (VDD33), U2.22 (VDD33), U2.25 (AVDD33), U2.34 (VDD33), U2.43 (VDD33), U2.[3,25] (AVDD33), U2.[12,22,34,43] (VDD33); also elsewhere on the board
+5V: C6.1, C7.1, C9.1, C10.1, D2.1 (C), D6.1 (C), J18.1, J19.1; also elsewhere on the board
/DC-SCI edge connector/DC-SCM_CLK_100M_1.CLK+: R143.2; also elsewhere on the board
/DC-SCI edge connector/DC-SCM_CLK_100M_1.CLK-: R144.2; also elsewhere on the board
/DC-SCI edge connector/DC-SCM_PCIE_LOCAL_USB.RX0+: R132.2; also elsewhere on the board
/DC-SCI edge connector/DC-SCM_PCIE_LOCAL_USB.RX0-: R133.2; also elsewhere on the board
/DC-SCI edge connector/DC-SCM_PCIE_LOCAL_USB.TX0+: R141.2; also elsewhere on the board
/DC-SCI edge connector/DC-SCM_PCIE_LOCAL_USB.TX0-: R142.2; also elsewhere on the board
/DC-SCI edge connector/~DC_SCM_STBY_RST: R188.2; also elsewhere on the board
/DC-SCI edge connector/~PCIE_HPM_SCM_PERST: TP14.1 (1_1), U2.47 (~PERST); also elsewhere on the board
/PCIe to USB/+3V3_FLASH: C39.1, D8.1 (C), R193.1, U5.8 (VCC)
/PCIe to USB/C_PETX+: C37.2, U2.4 (PETXP)
/PCIe to USB/C_PETX-: C38.2, U2.5 (PETXN)
/PCIe to USB/LOCAL_USB1.D+: D1.2, R195.2, U2.35 (U2DP1)
/PCIe to USB/LOCAL_USB1.D-: D1.1, R194.2, U2.36 (U2DM1)
/PCIe to USB/LOCAL_USB2.D+: D5.2, R197.2, U2.44 (U2DP2)
/PCIe to USB/LOCAL_USB2.D-: D5.1, R196.2, U2.45 (U2DM2)
/PCIe to USB/PECLK+: R143.1, U2.1 (PECLKP)
/PCIe to USB/PECLK-: R144.1, U2.2 (PECLKN)
/PCIe to USB/PERX+: R141.1, U2.7 (PERXP)
/PCIe to USB/PERX-: R142.1, U2.8 (PERXN)
/PCIe to USB/PETX+: C37.1, R132.1
/PCIe to USB/PETX-: C38.1, R133.1
/PCIe to USB/PPON1: TP16.1 (1_1), U2.20 (PPON1)
/PCIe to USB/PPON2: TP17.1 (1_1), U2.18 (PPON2)
/PCIe to USB/SPI_DI: J8.6 (SPI_MISO), R156.2, R160.1, U5.5 (SI/IO0)
/PCIe to USB/SPI_DO: J8.8 (SPI_MOSI), R157.2, R165.1, U5.2 (SO/IO1)
/PCIe to USB/SPI_SCK: J8.4 (SPI_SCK), R158.2, R183.2, U5.6 (SCLK)
/PCIe to USB/USB1_D+: J18.3, R195.1
/PCIe to USB/USB1_D-: J18.2, R194.1
/PCIe to USB/USB2_D+: J19.3, R197.1
/PCIe to USB/USB2_D-: J19.2, R196.1
/PCIe to USB/USB_FLASH_SPI.DI: R156.1, U2.16 (SPISI)
/PCIe to USB/USB_FLASH_SPI.DO: R157.1, U2.13 (SPISO)
/PCIe to USB/USB_FLASH_SPI.SCK: R158.1, U2.15 (SPISCK)
/PCIe to USB/USB_FLASH_SPI.~CS0: R159.1, U2.14 (~SPICS)
/PCIe to USB/XT1: C35.2, R154.2, U2.24 (XT1), Y1.1
/PCIe to USB/XT2: R155.2, U2.23 (XT2)
/PCIe to USB/~HOLD: R181.1, U5.7 (~HOLD/IO3)
/PCIe to USB/~OCI1: R151.1, U2.19 (~OCI1)
/PCIe to USB/~OCI2: R145.1, U2.17 (~OCI2)
/PCIe to USB/~PECREQ: R186.1, TP11.1 (1_1), U2.10 (~PECREQ)
/PCIe to USB/~PEWAKE: R185.1, TP12.1 (1_1), U2.48 (~PEWAKE)
/PCIe to USB/~SMI: R184.1, TP13.1 (1_1), U2.46 (~SMI)
/PCIe to USB/~SPI_CS: J8.2 (SPI_CS), R159.2, R182.1, U5.1 (~CS)
/PCIe to USB/~WP: R166.1, U5.3 (~WP/IO2)
GND: C6.2, C7.2, C9.2, C10.2, C11.2, C12.2, C13.2, C14.2, C19.2, C20.2, C21.2, C22.2, C23.2, C24.2, C29.2, C30.2, C31.2, C32.1, C33.1, C34.1, C35.1, C36.1, C39.2, D1.3, D2.2 (A), D5.3, D6.2 (A), J8.3 (GND), J8.5 (GND), J8.9 (GND), J18.4, J18.MP1, J18.MP2, J19.4, J19.MP1, J19.MP2, R140.1, R183.1, R189.2, R190.2, R191.2, R192.2, U2.27 (IC(L)), U2.49 (GND), U5.4 (VSS), U5.EP, Y1.2 (SH), Y1.4 (SH); also elsewhere on the board
unnamed: C36.2, R154.1, R155.1, Y1.3
unnamed: J8.1 (3V3), R193.2
unnamed: R140.2, U2.26 (RREF)
unnamed: R190.1, U2.32 (U3RXDN1)
unnamed: R192.1, U2.41 (U3RXDN2)
unnamed: R189.1, U2.31 (U3RXDP1)
unnamed: R191.1, U2.40 (U3RXDP2)
unnamed: R187.1, R188.1, TP15.1 (1_1), U2.11 (~PONRST)

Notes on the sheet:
Note: Compatible cable: Delock 84834
Configuration flash
USB2 2.0
USB1 2.0
PCIe to USB controller
